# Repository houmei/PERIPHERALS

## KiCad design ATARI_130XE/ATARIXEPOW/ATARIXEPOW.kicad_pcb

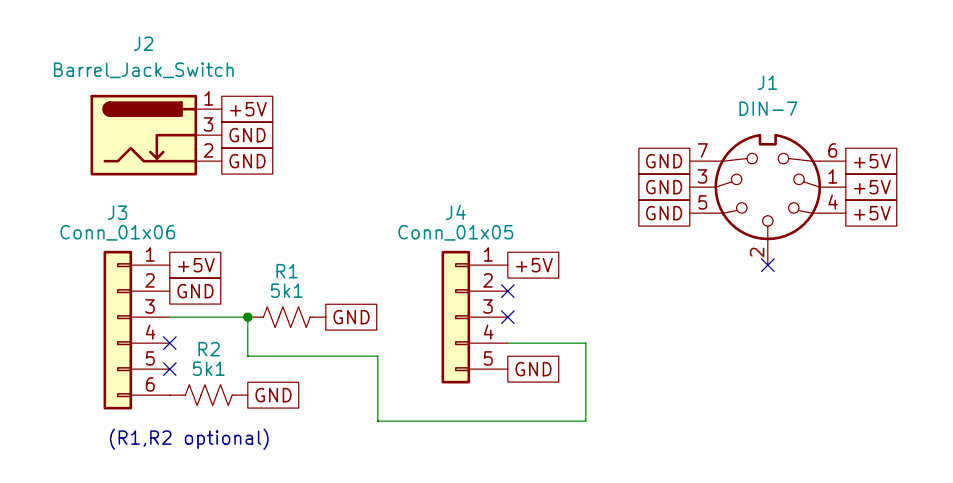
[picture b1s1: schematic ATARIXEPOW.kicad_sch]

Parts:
J1: DIN-7; DSCT-7-07F-S
J2: Barrel_Jack_Switch; BarrelJack_GCT_DCJ200-10-A_Horizontal
J3: Conn_01x06; PinHeader_1x06_P2.54mm_Vertical
J4: Conn_01x05; PinHeader_1x05_P2.54mm_Vertical
R1, R2: 5k1; R_Axial_DIN0204_L3.6mm_D1.6mm_P5.08mm_Horizontal

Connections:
+5V: J1.1, J1.4, J1.6, J2.1, J3.1, J4.1
GND: J1.3, J1.5, J1.7, J2.2, J2.3, J3.2, J4.5, R1.2, R2.2
unnamed: J3.3, J4.4, R1.1
unnamed: J3.6, R2.1

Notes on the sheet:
(R1,R2 optional)

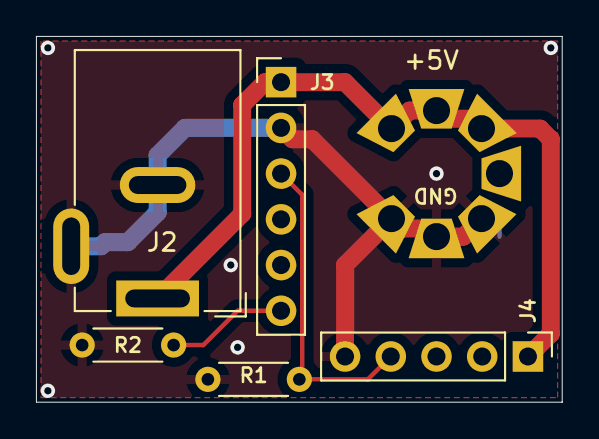
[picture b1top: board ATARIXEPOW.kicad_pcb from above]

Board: 2 copper layers, 29.2 x 20.3 mm, 6 parts (1 on the bottom side), 4 nets.
